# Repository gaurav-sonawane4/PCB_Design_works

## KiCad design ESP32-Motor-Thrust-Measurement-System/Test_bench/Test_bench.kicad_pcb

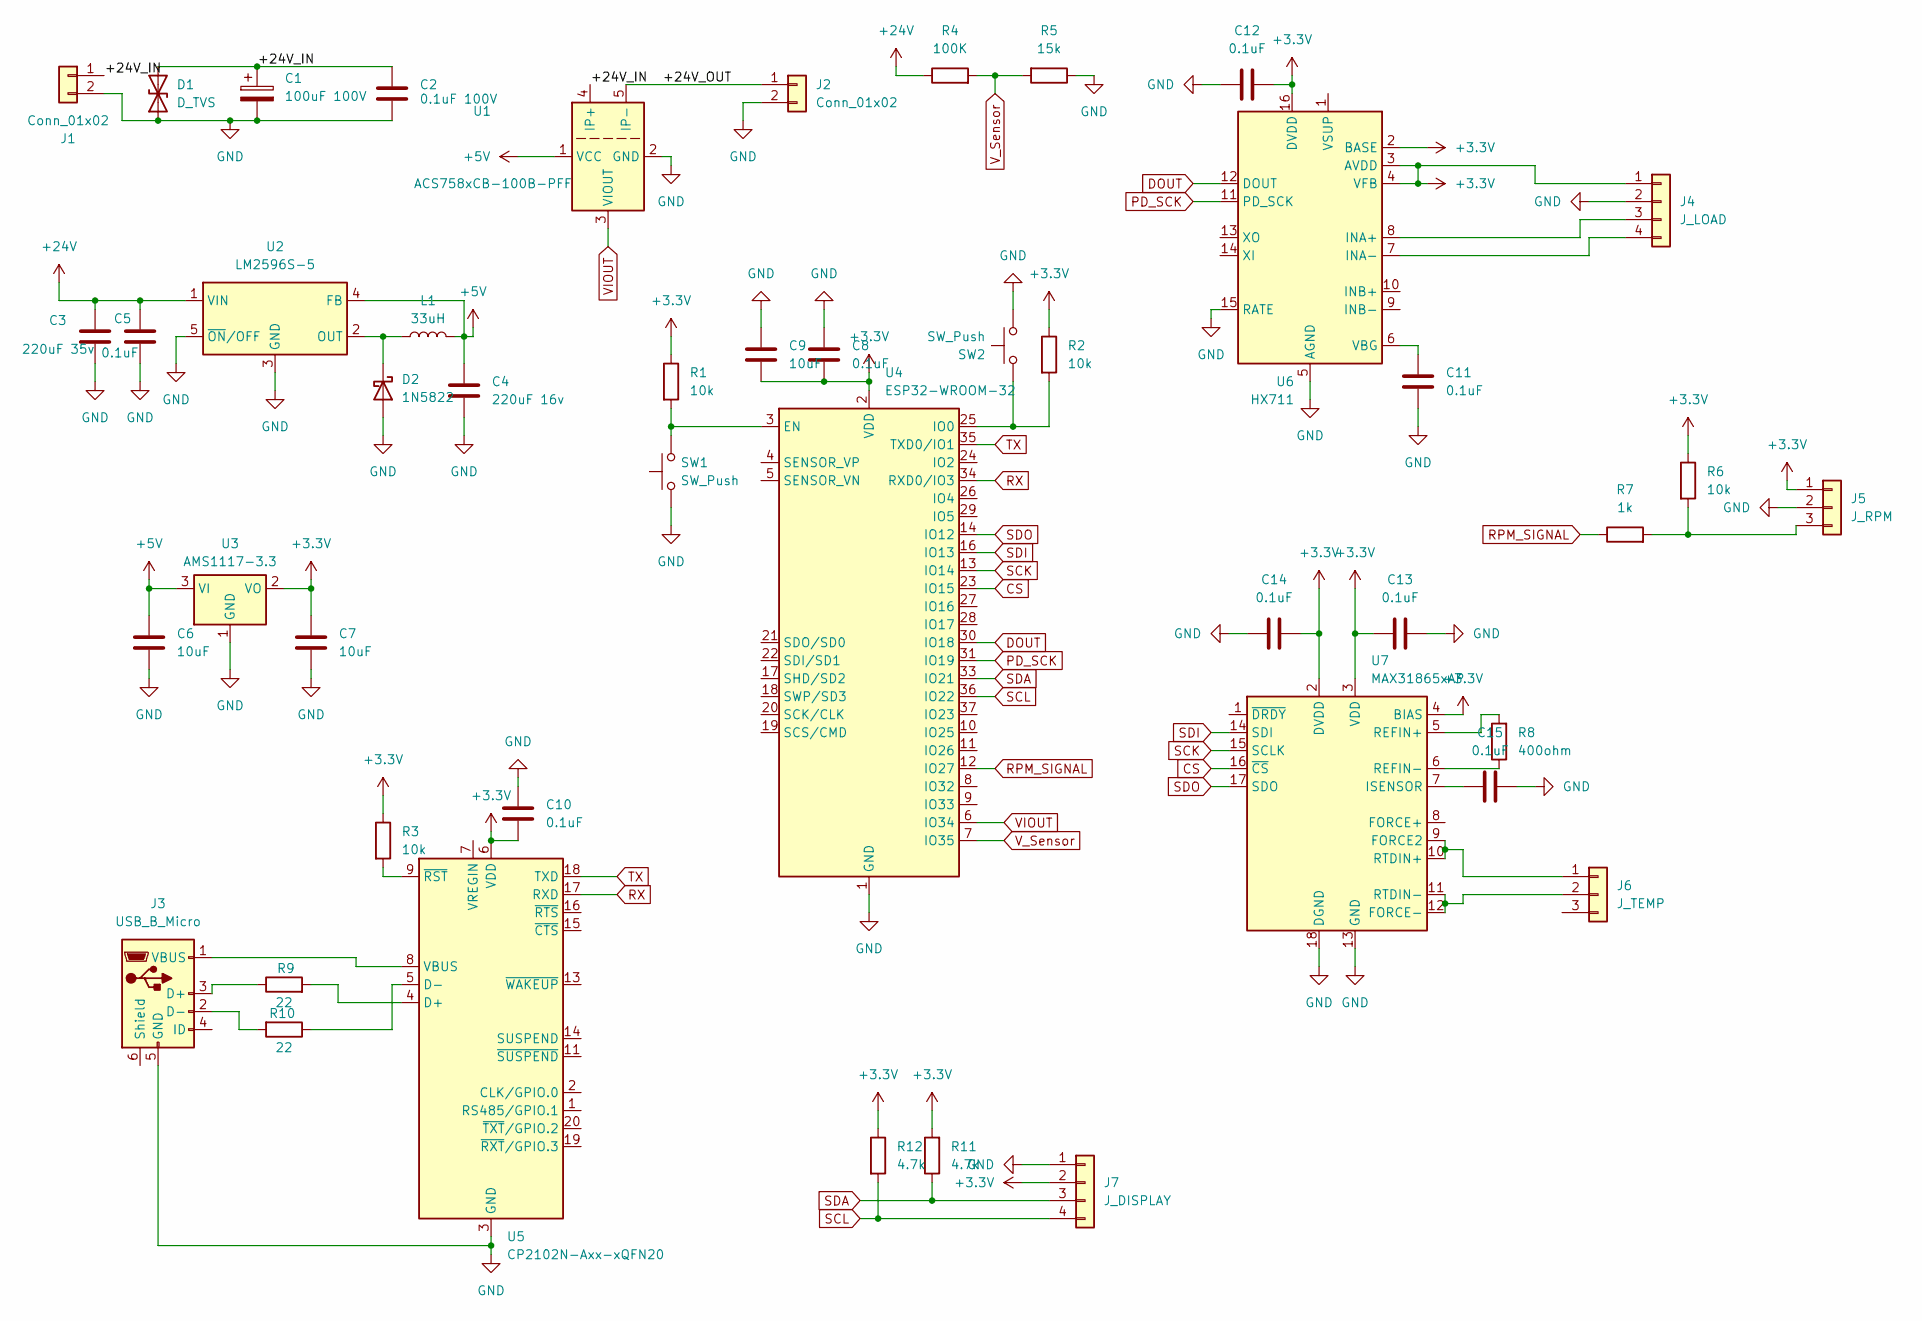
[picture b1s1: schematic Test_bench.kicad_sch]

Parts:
C1: 100uF 100V; CP_Radial_D10.0mm_P5.00mm
C2: 0.1uF 100V; C_1206_3216Metric
C3: 220uF 35v; C_Radial_D10.0mm_H12.5mm_P5.00mm
C4: 220uF 16v; C_Radial_D10.0mm_H12.5mm_P5.00mm
C5: 0.1uF; C_1206_3216Metric
C6, C7, C9: 10uF; C_1206_3216Metric
C8, C10, C11, C12, C13, C14, C15: 0.1uF; C_0805_2012Metric
D1: D_TVS; D_SMB
D2: 1N5822; D_DO-201AD_P15.24mm_Horizontal
J1: Conn_01x02; AMASS_XT60-F_1x02_P7.20mm_Vertical
J2: Conn_01x02; AMASS_XT60-M_1x02_P7.20mm_Vertical
J3: USB_B_Micro; USB_Micro-AB_Molex_47590-0001
J4: J_LOAD; JST_XH_B4B-XH-AM_1x04_P2.50mm_Vertical
J5: J_RPM; FanPinHeader_1x03_P2.54mm_Vertical
J6: J_TEMP; FanPinHeader_1x03_P2.54mm_Vertical
J7: J_DISPLAY; FanPinHeader_1x04_P2.54mm_Vertical
L1: 33uH; L_10.4x10.4_H4.8
R1, R2, R3, R6: 10k; R_0805_2012Metric
R4: 100K; R_0805_2012Metric
R5: 15k; R_0805_2012Metric
R7: 1k; R_0805_2012Metric
R8: 400ohm; R_0805_2012Metric
R9, R10: 22; R_0805_2012Metric
R11, R12: 4.7k; R_0805_2012Metric
SW1, SW2: SW_Push; SW_SPST_TL3342
U1: ACS758xCB-100B-PFF; Allegro_CB_PFF
U2: LM2596S-5; TO-263-5_TabPin3
U3: AMS1117-3.3; SOT-223-3_TabPin2
U4: ESP32-WROOM-32
U5: CP2102N-Axx-xQFN20; SiliconLabs_QFN-20-1EP_3x3mm_P0.5mm_EP1.8x1.8mm
U6: HX711; SOIC-16_3.9x9.9mm_P1.27mm
U7: MAX31865xAP; SSOP-20_5.3x7.2mm_P0.65mm

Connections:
+3.3V: C7.1, C8.2, C9.2, C10.2, C12.2, C13.2, C14.1, J4.1, J5.1, J7.2, R1.1, R2.1, R3.1, R6.1, R11.2, R12.1, U3.2 (VO), U4.2 (VDD), U5.6 (VDD), U6.2 (BASE), U6.3 (AVDD), U6.4 (VFB), U6.16 (DVDD), U7.2 (DVDD), U7.3 (VDD), U7.4 (BIAS)
+5V: C4.1, C6.1, L1.2, U1.1 (VCC), U2.4 (FB), U3.3 (VI)
+24V: C3.1, C5.1, R4.1, U2.1 (VIN)
/+24V_IN: C1.1, C2.1, D1.2 (A2), J1.1, U1.4 (IP+)
/+24V_OUT: J2.1, U1.5 (IP-)
CS: U4.23 (IO15), U7.16 (~CS)
DOUT: U4.30 (IO18), U6.12 (DOUT)
GND: C1.2, C2.2, C3.2, C4.2, C5.2, C6.2, C7.2, C8.1, C9.1, C10.1, C11.2, C12.1, C13.1, C14.2, C15.2, D1.1 (A1), D2.2 (A), J1.2, J2.2, J3.5 (GND), J4.2, J5.2, J7.1, R5.1, SW1.1, SW2.2, U1.2 (GND), U2.3 (GND), U2.5 (~ON/OFF), U3.1 (GND), U4.1 (GND), U4.15 (GND), U4.38 (GND), U4.39 (GND), U5.3 (GND), U5.12 (GND), U5.21 (GND), U6.5 (AGND), U6.15 (RATE), U7.13 (GND), U7.18 (DGND), U7.19 (GND)
unnamed: D2.1 (K), L1.1, U2.2 (OUT)
unnamed: J3.3 (D+), R9.1
unnamed: J3.2 (D-), R10.2
unnamed: J3.1 (VBUS), U5.8 (VBUS)
unnamed: J4.3, U6.8 (INA+)
unnamed: J4.4, U6.7 (INA-)
unnamed: J5.3, R6.2, R7.2
unnamed: J6.1, U7.9 (FORCE2), U7.10 (RTDIN+)
unnamed: J6.2, U7.11 (RTDIN-), U7.12 (FORCE-)
unnamed: R1.2, SW1.2, U4.3 (EN)
unnamed: R2.2, SW2.1, U4.25 (IO0)
unnamed: R9.2, U5.4 (D+)
unnamed: R10.1, U5.5 (D-)
unnamed: R3.2, U5.9 (~RST)
unnamed: C11.1, U6.6 (VBG)
unnamed: C15.1, U7.7 (ISENSOR)
unnamed: R8.2, U7.5 (REFIN+)
unnamed: R8.1, U7.6 (REFIN-)
PD_SCK: U4.31 (IO19), U6.11 (PD_SCK)
RPM_SIGNAL: R7.1, U4.12 (IO27)
RX: U4.34 (RXD0/IO3), U5.17 (RXD)
SCK: U4.13 (IO14), U7.15 (SCLK)
SCL: J7.4, R12.2, U4.36 (IO22)
SDA: J7.3, R11.1, U4.33 (IO21)
SDI: U4.16 (IO13), U7.14 (SDI)
SDO: U4.14 (IO12), U7.17 (SDO)
TX: U4.35 (TXD0/IO1), U5.18 (TXD)
VIOUT: U1.3 (VIOUT), U4.6 (IO34)
V_Sensor: R4.2, R5.2, U4.7 (IO35)

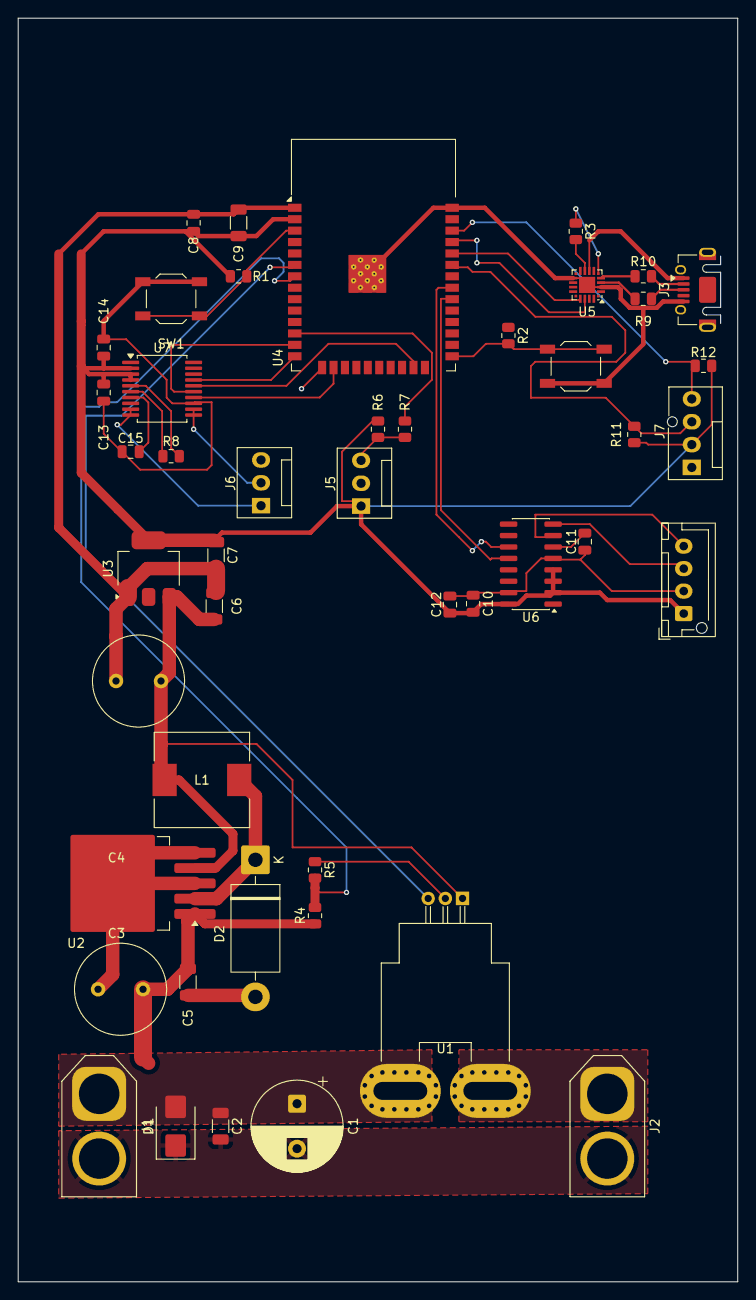
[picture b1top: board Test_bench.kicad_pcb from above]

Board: 2 copper layers, 80.0 x 140.4 mm, 46 parts (0 on the bottom side), 37 nets.
